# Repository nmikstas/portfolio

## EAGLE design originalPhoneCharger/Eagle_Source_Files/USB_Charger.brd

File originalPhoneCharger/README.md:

# original-phone-charger
A li-po battery based phone charger

# NOTE
This project is part of my project portfolio: https://nmikstas.github.io/portfolio/

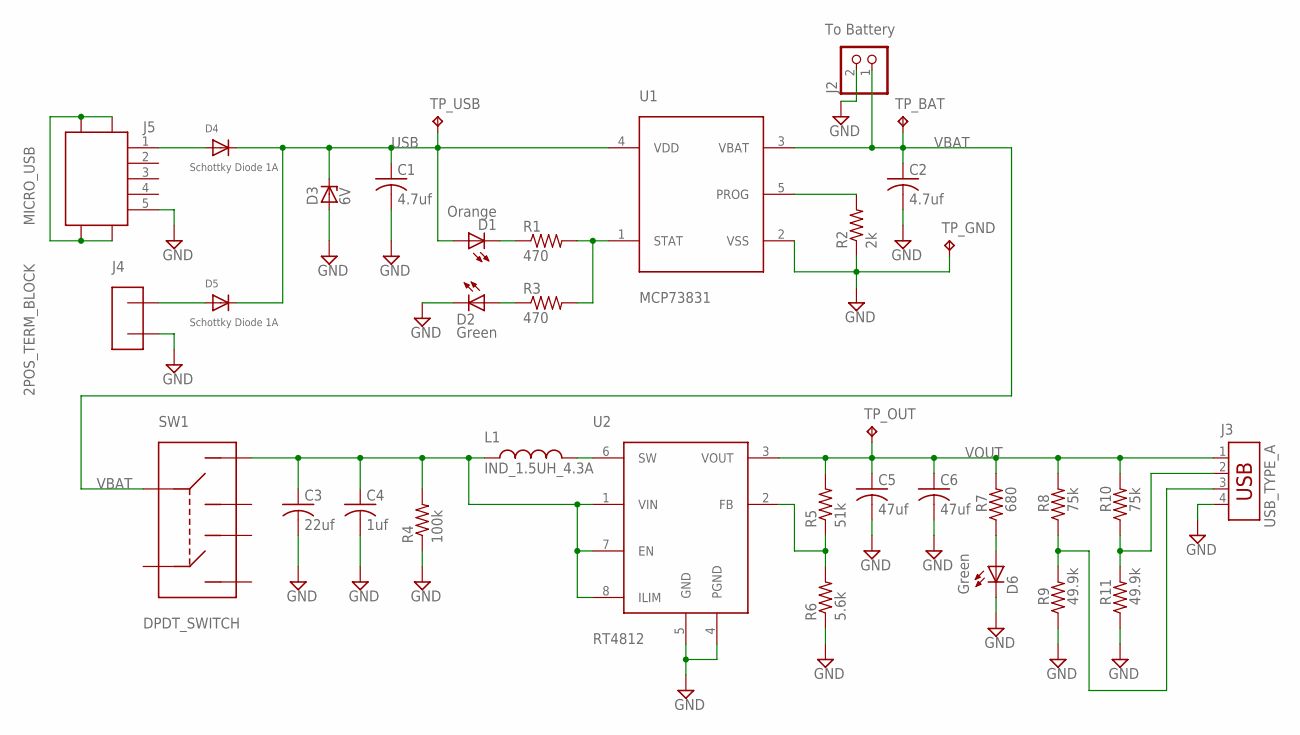
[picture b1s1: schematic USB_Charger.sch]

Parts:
C1, C2: 4.7uf; C0805
C3: 22uf; C0805
C4: 1uf; C0805
C5, C6: 47uf; C1210
D1: Orange; CHIP-LED0805
D2, D6: Green; CHIP-LED0805
D3: 6V; SMB
D4, D5: Schottky Diode 1A; SMADIODE
J2: To Battery; JST-PH-2-THM-RA
J3: USB_TYPE_A; USB
J4: 2POS_TERM_BLOCK; 2POS_5.08MM
J5: MICRO_USB
L1: IND_1.5UH_4.3A; IND_SMD
R1, R3: 470; R0805
R2: 2k; R0805
R4: 100k; R0805
R5: 51k; R0805
R6: 5.6k; R0805
R7: 680; R0805
R8, R10: 75k; R0805
R9, R11: 49.9k; R0805
SW1: DPDT_SWITCH; GF-126-0159
TP_BAT: TPB1,27; B1,27
TP_GND: TPB1,27; B1,27
TP_OUT: TPB1,27; B1,27
TP_USB: TPB1,27; B1,27
U1: MCP73831; SOT-23-5
U2: RT4812; TSOT-23-8

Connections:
GND: C1.2, C2.2, C3.2, C4.2, C5.2, C6.2, D2.C, D3.A, D6.C, J2.2 (1), J3.4, J4.2, J5.5, R2.1, R4.1, R6.1, R9.1, R11.1, TP_GND.TP, U1.2 (VSS), U2.4 (PGND), U2.5 (GND)
IND_OUT: L1.2, U2.6 (SW)
unnamed: R5.1, R6.2, U2.2 (FB)
unnamed: D1.C, R1.1
unnamed: R1.2, R3.2, U1.1 (STAT)
unnamed: R2.2, U1.5 (PROG)
unnamed: D5.A, J4.1
unnamed: D2.A, R3.1
unnamed: D6.A, R7.1
unnamed: J3.3, R8.1, R9.2
unnamed: J3.2, R10.1, R11.2
SW_OUT: C3.1, C4.1, L1.1, R4.2, SW1.1, U2.1 (VIN), U2.7 (EN), U2.8 (ILIM)
USB: C1.1, D1.A, D3.C, D4.C, D5.C, TP_USB.TP, U1.4 (VDD)
USB_IN: D4.A, J5.1
USB_SHD: J5.SH1, J5.SH2, J5.SH3, J5.SH4
VBAT: C2.1, J2.1 (2), SW1.2, TP_BAT.TP, U1.3 (VBAT)
VOUT: C5.1, C6.1, J3.1, R5.2, R7.2, R8.2, R10.2, TP_OUT.TP, U2.3 (VOUT)

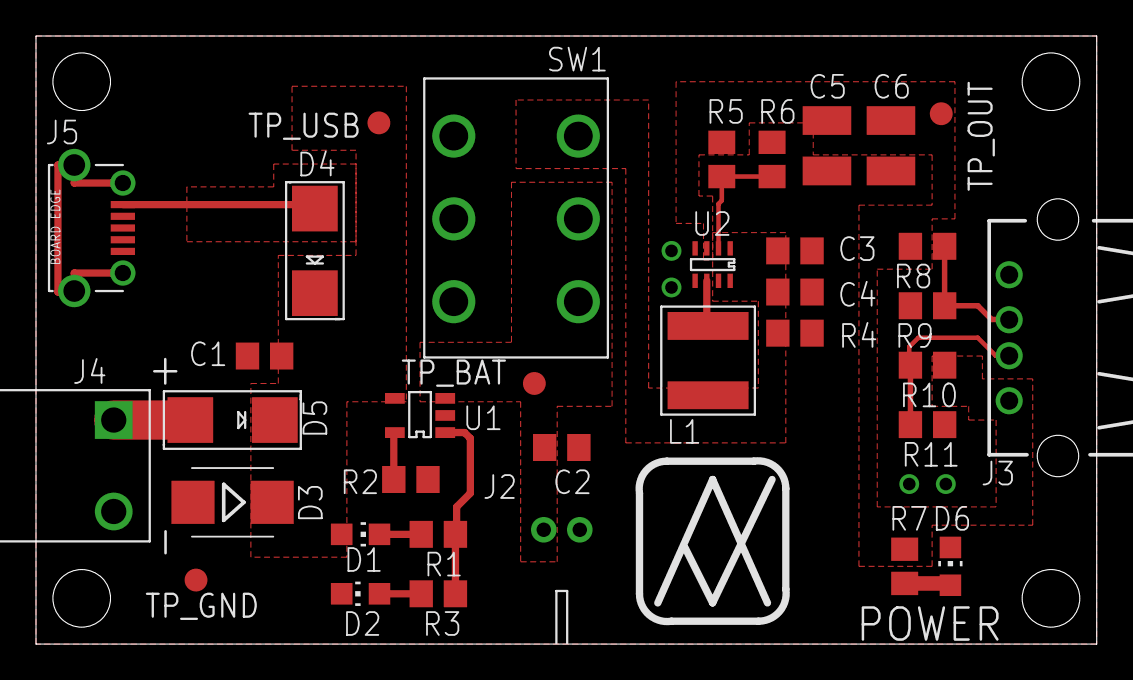
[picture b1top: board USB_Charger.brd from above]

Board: 2 copper layers, 58.9 x 33.8 mm, 35 parts (0 on the bottom side), 17 nets.

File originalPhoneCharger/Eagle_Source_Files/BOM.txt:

Partlist

Exported from USB_Charger.brd at 4/19/2016 1:48 PM

EAGLE Version 7.5.0 Copyright (c) 1988-2015 CadSoft

Assembly variant: 

Part     Value             Package         Library     Position (inch)       Orientation

C1       4.7uf             C0805           rcl         (0.5 0.63)            R180
C2       4.7uf             C0805           rcl         (1.15 0.43)           R0
C3       22uf              C0805           rcl         (1.66 0.86)           R0
C4       1uf               C0805           rcl         (1.66 0.77)           R0
C5       47uf              C1210           rcl         (1.73 1.09)           R270
C6       47uf              C1210           rcl         (1.87 1.09)           R270
D1       Orange            CHIP-LED0805    led         (0.71 0.24)           R270
D2       Green             CHIP-LED0805    led         (0.71 0.11)           R90
D3       6V                SMB             diode       (0.43 0.31)           R180
D4       Schottky Diode 1A SMADIODE        adafruit    (0.61 0.86)           R90
D5       Schottky Diode 1A SMADIODE        adafruit    (0.43 0.49)           R180
D6       Green             CHIP-LED0805    led         (2 0.17)              R0
J2       To Battery        JST-PH-2-THM-RA adafruit    (1.15 0.25)           R180
J3       USB_TYPE_A        USB             con-amp     (2.64 0.67)           R90
J4       2POS_TERM_BLOCK   2POS_5.08MM     USB_Charger (0.17 0.39)           R0
J5       MICRO_USB         MICRO_USB       USB_Charger (0.19 0.91)           R0
L1       IND_1.5UH_4.3A    IND_SMD         USB_Charger (1.47 0.62)           R90
R1       470               R0805           rcl         (0.88 0.24)           R0
R2       2k                R0805           rcl         (0.82 0.36)           R180
R3       470               R0805           rcl         (0.88 0.11)           R0
R4       100k              R0805           rcl         (1.66 0.68)           R180
R5       51k               R0805           rcl         (1.5 1.06)            R90
R6       5.6k              R0805           rcl         (1.61 1.06)           R270
R7       680               R0805           rcl         (1.9 0.17)            R90
R8       75k               R0805           rcl         (1.95 0.87)           R180
R9       49.9k             R0805           rcl         (1.95 0.74)           R0
R10      75k               R0805           rcl         (1.95 0.61)           R0
R11      49.9k             R0805           rcl         (1.95 0.48)           R180
SW1      DPDT_SWITCH       GF-126-0159     USB_Charger (1.05 0.93)           R90
TP_BAT   TPB1,27           B1,27           testpad     (1.09 0.57)           R0
TP_GND   TPB1,27           B1,27           testpad     (0.35 0.14)           R0
TP_OUT   TPB1,27           B1,27           testpad     (1.98 1.16)           R0
TP_USB   TPB1,27           B1,27           testpad     (0.75 1.14)           R90
U1       MCP73831          SOT-23-5        USB_Charger (0.84 0.5)            R90
U2       RT4812            TSOT-23-8       USB_Charger (1.48 0.83)           R180

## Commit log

2019-10-14 Created the home page
2019-10-15 Created a resume page
2019-10-15 Added PDF version of resume
2019-10-15 Fixed a minor styling problem
2019-10-15 Added web programming portfolio objects
2019-10-15 Fixed the weather image
2019-10-15 Added sick target effect to web portfolio page
2019-10-15 modified target effect
2019-10-16 Made minor changes to the web programming page
2019-10-16 Changed the target style
2019-10-16 Changed class constants to static get functions
2019-10-17 Modified the styling
2019-10-25 Added babylon home page
2019-10-25 Slowed down the carousel glow effect
2019-10-26 Added red lights and animations
2019-10-27 added link fadeout when slide is clicked
2019-10-27 modified the picking functions
2019-10-27 Added fog effects
2019-10-27 Tweeked the animations
2019-10-29 Added links to projects on every topic page
2019-10-29 Added Metroid page
2019-10-30 Added potentiostat page
2019-10-30 Fixed some minor styling bugs
2019-10-30 Changes picture background colors
2019-10-31 Added game controller page
2019-10-31 Transferred project into GitHub
2019-10-31 Added OSR USB FX2 Linux Driver Page
2019-10-31 Added talking clock page
2019-10-31 Added link to talking clock page
2019-11-01 Added landing pages for many of the projects
2019-11-01 Added langing pages for all the projects
2019-11-05 Added the super mario music web page
2019-11-05 Added FPGA Filter Implementation webpage
2019-11-05 Troubleshooting
2019-11-07 Added NMPSM3 page
2019-11-08 Added a simple pipelined processor page
2019-11-11 Added OSR reverse engineering page
2019-11-11 Added enhanced phone charger page
2019-11-12 Added Zigbee carrier page
2019-11-12 Added a Zigmee Linux API page
2019-11-12 Trnasferred project into GitHub
2019-11-12 Added thermal runaway detector/interruptor page
2019-11-12 Added images for LCD board and RS232/RS485 projects
2019-11-12 Added LCD demo page
2019-11-12 Added USB to serial page
2019-11-18 Added the dragon warrior disassembly page
2019-11-18 Added DSP in FPGA images
2019-11-20 Created landing page for DSP in FPGA
2019-11-21 Greated FIR filter page
2019-11-21 Added DUC and DDS pages
2019-11-21 Added DDC page
2019-11-21 Added HLS Viterbi Decoder page
2019-11-21 Added farmer lab page
2019-11-22 Added a CMOS Camera page
2019-11-22 Updated resume
2019-12-13 Started adding sound effects to the home page
2019-12-13 Fixed a reset bug
2019-12-13 Added more sound effects
2019-12-14 Added alarm sound effects
2019-12-14 Modified the SFX
2019-12-16 Added more links in the web portion of the portfolio
2019-12-16 Added star wars audio disassembly page
2019-12-16 Added images for the Asteroids web pages
2019-12-17 Added Asteroids disassembly page
2019-12-17 Added an Asteroids HDL page
2019-12-17 Added an Asteroids PCB page
2020-01-02 Added the mongo scraper link
2020-01-25 Added github link and modified the styling
2020-03-15 Added nt3d link
2020-03-15 Added nt 2d page
2020-03-15 Added ntnt link
2020-03-16 Added AVG link
2020-03-17 Added AVG images
2020-03-17 Added AVG CPLD info
2020-03-17 Added TTL design to the AVG page
2020-03-21 Began a visual overview section for NTNT and YASS
2020-03-21 Worked on the visual overview of NTNT
2020-03-22 Added loading gif
2020-03-22 Added Google book search project
2020-03-22 Fixed YASS header
2020-03-22 Added NTNT renderer visual overview
2020-03-22 Added more to the NTNT visual overview
2020-03-22 Finished the NTNT visual overview
2020-03-25 Added YASS Overview
2020-04-22 Added link to canvas date/time picker
2020-05-18 Added my web resume
2020-05-26 Fixed simple pipelined processor repository link
2020-06-11 Updated the dragon warrior disassembly section
2020-06-28 Updated the Dragon Warrior completion map
2020-07-25 Updated the dragon warrior section to show completion
2020-09-27 Added heterodyne section
2020-09-27 Added more content to the heterodyne webpage
2020-09-27 Finished the heterodyne page
2020-09-27 Fixed some typos
2021-05-12 Worked on a belt alignment app
2021-05-12 Cleaned up the existing code
2021-05-12 Fixed some spelling errors
2021-05-13 Added the calculations and a clear button
2021-05-17 Began working on the plotting class
2021-05-17 Added scaling indicators to the graph
2021-05-17 Added movements and starrett graduations
2021-05-17 Changed background color of plot to white
2021-05-18 Added movement end points and adjusted the transparancies
2021-05-18 Added source code link to web page
2021-05-19 Began the shaft alignment page
2021-05-19 Added the plot class
2021-05-25 Added dials to the shaft alignment page
2021-05-25 Finished the movement calculations on the shaft alignment page
2021-05-26 Continued work on the graphing function
2021-05-26 Finished the plotting in the shaft alignment page
2021-05-26 Added mechanical landing page
2021-05-26 Fixed typos
2021-08-25 Updated precision belt alignment for multiple entries
2021-08-30 Added multiple adjustment support to the belt alignment plotting
2021-08-31 Finished multiple adjustments and began adding multiple measurements
2021-09-01 Finished measurements and cost analysis
2021-09-01 Completed load data functionality for adjustments
2021-09-01 Completed load data functionality
2021-09-06 Added print functionality
2021-09-20 Added dynamic headers to options and X,Y,Z to measurements
2021-09-20 Added X,Y,Z to print measurements
2022-01-27 Fixed printing format, always shows 3 movement options and clears error colors when loading data file
2022-01-27 Changed text to always display option 2 and option 3
2022-03-13 Removed mongo scraper
2022-03-13 Rearranged web portfolio page
2022-03-14 Updated projects on the web projects page
2022-05-18 Began work on a new word game
2022-05-18 Added bootstrap
2022-05-19 Worked on game settings modal
2022-05-25 Began working on layout
2022-05-25 Worked on sliders
2022-05-29 Finished column swap routine
2022-05-31 Finished column swapping and row shifting
2022-05-31 Finished 2nd step of evaluations
2022-06-01 Fixed some bugs
2022-06-01 Working on swap chain algorithms
2022-06-06 Finished phse 3 of the verification process
2022-06-06 Finished phase 4 of the verification process
2022-06-07 Finished verification process
2022-06-07 Fixed verification bug
2022-06-08 Worked on bug fixes
2022-06-12 Separated out game generation class
2022-06-13 Began separating out game engine class
2022-06-17 Kept separating everything into classes
2022-06-17 cleaned up more functions and continued to separate the renderer from the engine
2022-06-18 Continued separating out the classes
2022-06-22 Updated event listeners
2022-06-22 Finished separating out the game engine and game renderer classes
2022-06-23 Began changing renderer
2022-06-24 Adjusted the styling
2022-06-27 Finished swap and scroll animations
2022-06-27 Fixed a bug with the bolded letters
2022-06-27 Fixed a bug with the background opacity during a column swap
2022-06-27 Fixed evaluation animations
2022-06-27 Changed default game parameters
2022-06-28 Fixed animation bug
2022-06-28 Added column swap and scroll at the same time
2022-06-28 Made first selected column always on top when moving
2022-06-29 Midified layout of game board
2022-06-30 Fixed a rendering bug
2022-07-04 Added win lose and play states, tries remaining counter and changed the random word selection
2022-07-27 Began working on scoring
2022-07-27 Continued with scoring
2022-07-27 Finished scoring
2022-08-03 Changed some animation mechanisms
2022-08-03 Fixed more animation bugsa
2022-08-03 Fixed more animation bugs
2022-09-07 Fixed remaining graphical glitch
2022-09-22 Working on Whazzle instructions
2022-09-25 Finished Whazzle instructions
2022-10-05 Fixed instruction image sizing
2022-10-05 Added game object copying
2022-10-05 changed background color
2022-10-05 Put usedLettersArray inside game object
2022-10-24 Fixed errors in Whazzle game engine
2022-12-01 Worked on game generator
2022-12-02 Worked on game editor
2022-12-05 Finished game editor
2022-12-13 Updated the belt and shaft alignment pages
2022-12-13 Added source links for belt and shaft alignment
2022-12-14 Fixed Github link on main page
2023-05-26 Added Ultima 3 map viewer
2023-09-30 Updated map viewer to show data from an unused map
2024-06-22 Added 3 phase power simulator
2024-06-23 Cleaned up the phasor diagram
2024-06-24 Centered phasor
2024-07-09 Added neutral current calculations
2024-07-09 Began working on delta calculations
2024-07-11 Worked on delta voltage calculations
2024-07-12 Completed delta phasor calculations
2024-07-13 Cleaned up the phasor text
2024-07-13 Added KVL constraints to the delta line voltages
2024-07-14 Finished adding all components to delta calculation
2024-07-16 Fixed bug in 3 phase simulator
2024-07-17 Fixed power polarities in 3phaseSim
2024-07-18 Completed transformer simulation
2024-07-18 Fixed graphics
2024-07-20 Updating portfolio projects
2024-07-21 Consolidating old projects
2024-07-21 Added 3-phase power stuff to web.html
2024-07-21 Updated games portion of portfolio
2024-07-27 Updated portfolio
2024-08-01 Worked on symmetrical components
2024-08-02 Completed symmetrical components page
2024-08-03 Fixed a minor ug in the zero sequence graph
2024-08-03 Updated phasor presentation
2024-08-03 Updated phasor viewable components
2024-08-04 Added symmetrical components link to portfolio
2024-08-04 Fixed symmetrical components reset button
